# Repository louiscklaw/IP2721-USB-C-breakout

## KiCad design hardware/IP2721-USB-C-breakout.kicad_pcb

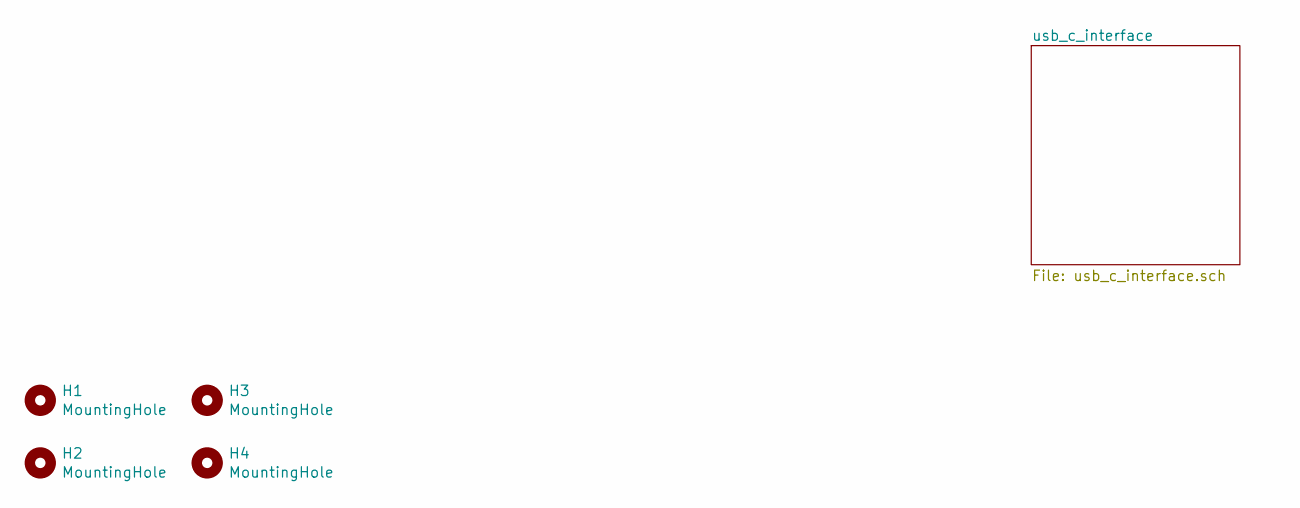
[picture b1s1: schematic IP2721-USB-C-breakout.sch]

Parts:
H1, H2, H3, H4: MountingHole; MountingHole_3.2mm_M3,rpi_like

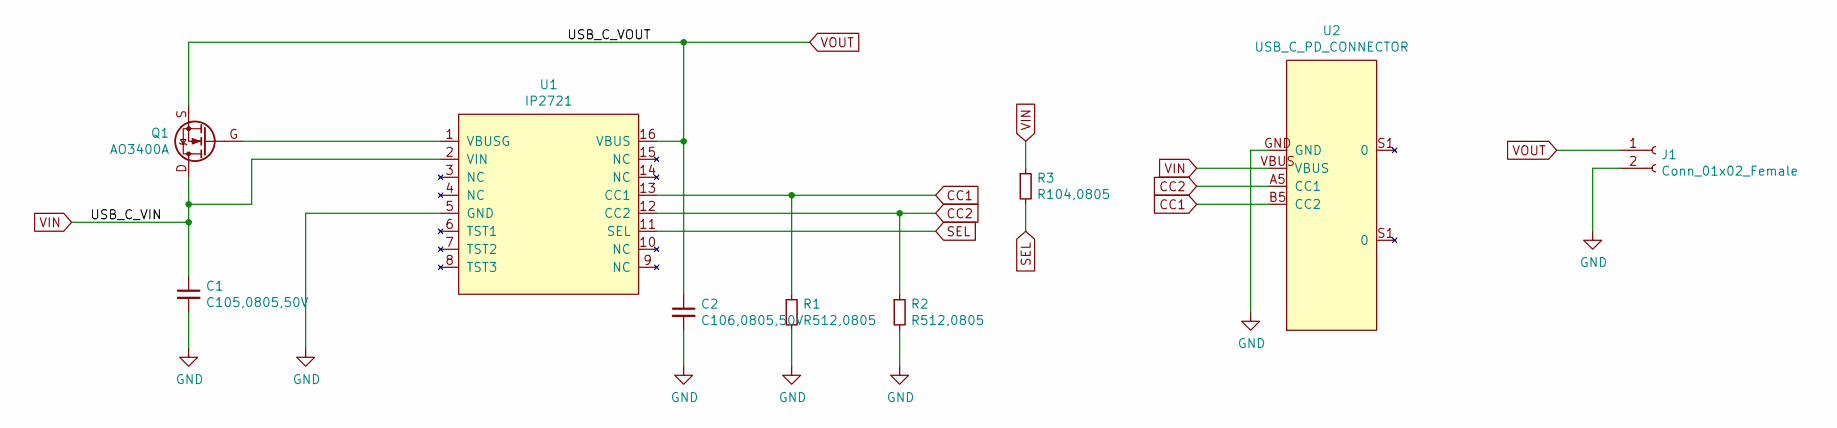
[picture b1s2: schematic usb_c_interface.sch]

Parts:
C1: C105,0805,50V; C_0805_2012Metric_Pad1.18x1.45mm_HandSolder
C2: C106,0805,50V; C_0805_2012Metric_Pad1.18x1.45mm_HandSolder
J1: Conn_01x02_Female; PinHeader_1x02_P2.54mm_Vertical
Q1: AO3400A; AO3400,SOT23
R1, R2: R512,0805; R_0805_2012Metric_Pad1.20x1.40mm_HandSolder
R3: R104,0805; R_0805_2012Metric_Pad1.20x1.40mm_HandSolder
U1: IP2721; TSSOP-16_4.4x5mm_P0.65mm
U2: USB_C_PD_CONNECTOR; USBC_16PIN

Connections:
CC1: R1.1, U1.13 (CC1), U2.B5 (CC2)
CC2: R2.1, U1.12 (CC2), U2.A5 (CC1)
GND: C1.2, C2.2, J1.2, R1.2, R2.2, U1.5 (GND), U2.GND
unnamed: Q1.G, U1.1 (VBUSG)
SEL: R3.2, U1.11 (SEL)
VIN: C1.1, Q1.D, R3.1, U1.2 (VIN), U2.VBUS
VOUT: C2.1, J1.1, Q1.S, U1.16 (VBUS)

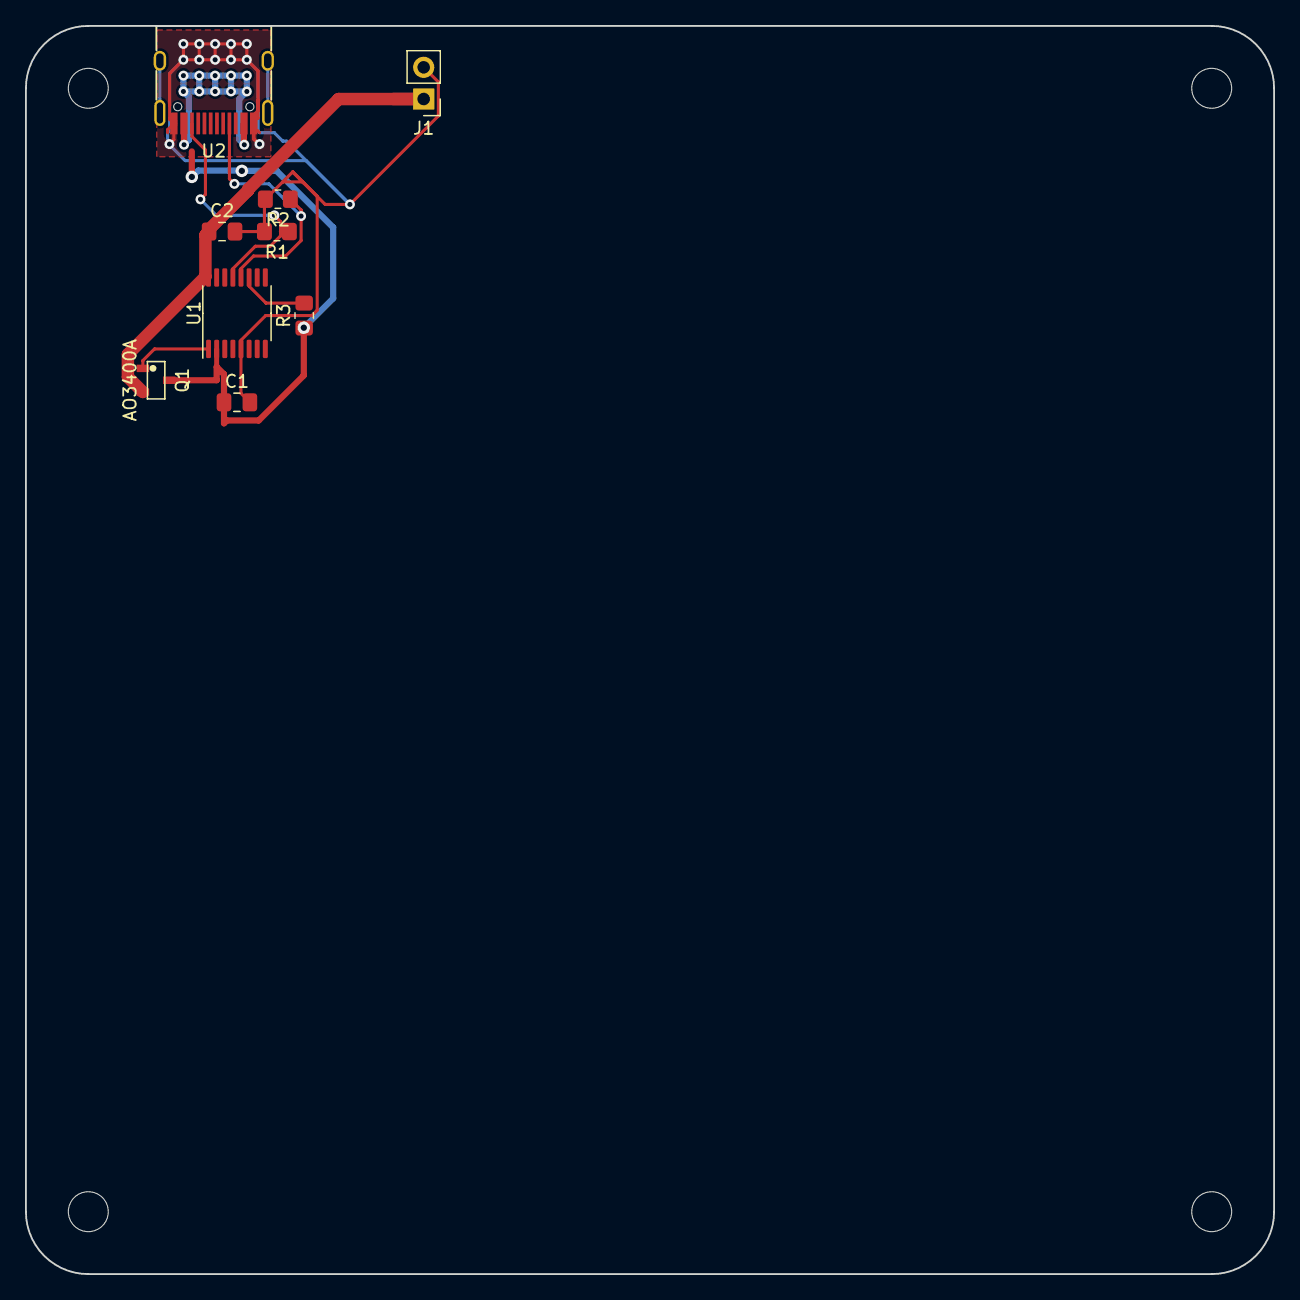
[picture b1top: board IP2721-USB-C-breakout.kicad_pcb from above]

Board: 2 copper layers, 100.0 x 100.0 mm, 13 parts (0 on the bottom side), 7 nets.

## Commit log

2021-09-19 update and test,
2021-09-19 update,
